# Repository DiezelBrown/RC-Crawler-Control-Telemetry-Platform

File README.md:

# RC Crawler Telemetry Platform
**Project Status:** 🚧 Active Development
<table align="center">
<tr>
<td align="center">
<br>
<b>Custom RC Crawler</b>
</td>

<td align="center">
<br>
<b>Live Telemetry Dashboard</b>
</td>
</tr>
</table>

A custom-built 1/10 scale RC crawler designed to demonstrate embedded systems, wireless telemetry, and real-time vehicle monitoring. The platform combines custom mechanical fabrication with ESP32 firmware, onboard sensors, and Bluetooth Low Energy (BLE) communication.

---

## Features

- ✅ Custom-fabricated steel chassis
- ✅ ESP32 embedded telemetry platform
- ✅ Battery voltage monitoring
- ✅ Motor temperature monitoring
- ✅ Wheel RPM measurement
- ✅ Vehicle speed calculation
- ✅ BNO055 IMU (Pitch & Roll)
- ✅ Bluetooth Low Energy (BLE)
- ✅ Mobile application 
- 🔄  Custom KiCad PCB *(In Progress)*
- ⏳ Operator-assisted recovery mode

---

## Technologies

- C++
- ESP32
- PlatformIO
- Bluetooth Low Energy (BLE)
- Embedded Systems
- Sensor Integration
- I²C
- OneWire
- Hall Effect Sensor
- MIG Welding

---

## Current Telemetry

| Feature | Status |
|----------|--------|
| Battery Voltage | ✅ |
| Motor Temperature | ✅ |
| Wheel RPM | ✅ |
| Vehicle Speed | ✅ |
| Pitch | ✅ |
| Roll | ✅ |
| Bluetooth | ✅ |

---

## Repository Structure

```text
firmware/
├── ESP32 firmware

hardware/
├── BOM.md
├── HARDWARE.md
├── pinout.md
└── wiring.md

docs/
├── Development updates
└── Testing results

photos/
├── Build photos
└── Demonstrations
```

---

## Current Status

### Completed

- ✅ Steel chassis
- ✅ ESP32 firmware
- ✅ Battery voltage sensor
- ✅ DS18B20 temperature sensor
- ✅ Hall-effect RPM sensor
- ✅ BNO055 IMU
- ✅ Bluetooth Low Energy
- ✅  Mobile telemetry application
### In Progress

- 🔄Custom KiCad PCB

### Planned

- ⏳ Operator-assisted recovery mode
- ⏳ Data logging

---

## Future Goals

- Develop a cross-platform mobile application.
- Design a custom KiCad PCB.
- Implement Bluetooth-based operator controls.
- Develop an operator-assisted recovery mode.

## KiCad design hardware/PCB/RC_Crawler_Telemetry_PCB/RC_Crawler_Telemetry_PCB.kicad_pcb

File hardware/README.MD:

# Hardware

## Chassis & Structure
- Custom welded steel chassis
- 5/16 in steel tubing
- 3/16 in steel tubing
- Pothyes CNC aluminum center frame brace / skid plate / transmission mount

## Drivetrain
- INJORA complete SCX10 II gearbox transmission
- 13T pinion gear
- Alloy front steering axle with steel gears (SCX10 II)
- Alloy rear axle with steel gears (SCX10 II)
- MEUS Racing SCX10 II 313 mm link set
- HopsupRC steel driveshaft set (85–122 mm and 95–137 mm)
- HOPLEX heavy-duty driveshaft (125–185 mm)

## Suspension & Steering
- INJORA DRX 100 mm dual-rate oil shocks (4)
- LJWRC 30 kg waterproof digital steering servo

## Wheels & Tires
- 1.9 in aluminum beadlock wheels
- 4.61 in soft rubber crawler tires

## Power System
- HobbyFans S3650 4300KV brushless motor
- HobbyFans 60A waterproof brushless ESC
- ESC programming card
- OVONIC 2S 7.4V 5200 mAh 50C LiPo battery
- Buck converter (5V power for ESP32)

## Radio System
- DumboRC X4 transmitter
- DumboRC X6F receiver

## Telemetry System
- ESP32 DevKit V1
- Battery voltage sensor
- DS18B20 waterproof temperature sensor
- Hall-effect RPM sensor
- BNO055 IMU *(planned)*
- Bluetooth mobile application *(in development)*
- Custom telemetry PCB *(planned)*

## Fasteners & Hardware
- 25 mm mounting screws
- Assorted metric screws
- Lock nuts
- Servo horn
- Steering linkage hardware
- Shock mounting hardware

## Wiring & Electronics
- Breadboard (prototype)
- Jumper wires (prototype)
- Silicone wire *(planned)*
- JST connectors *(planned)*

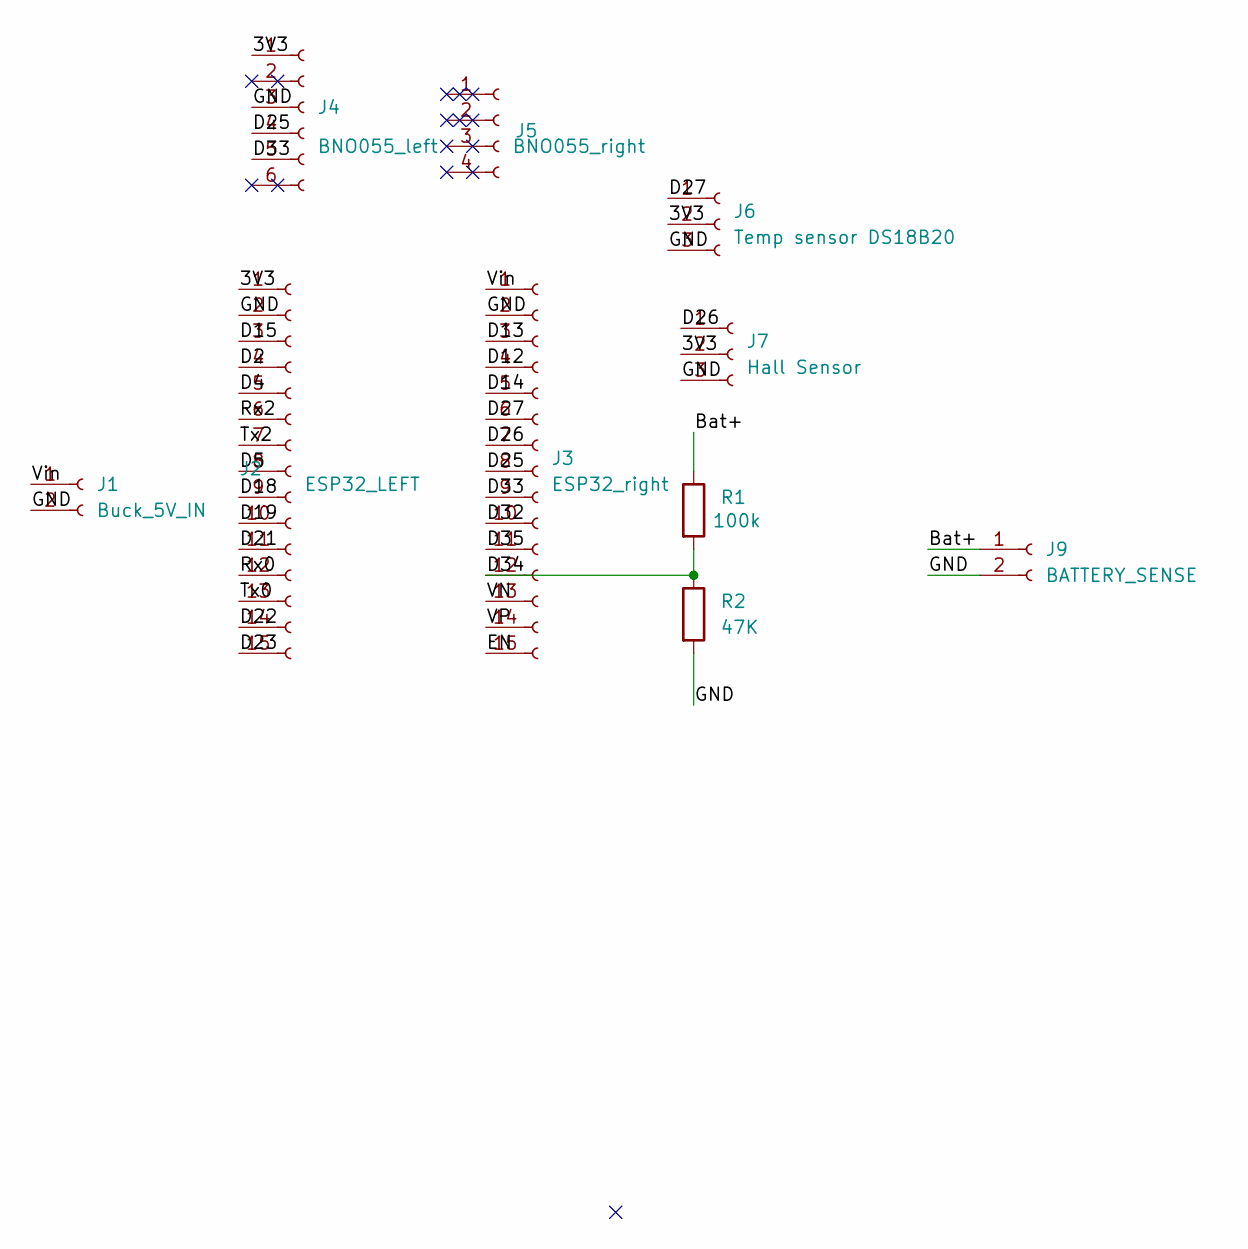
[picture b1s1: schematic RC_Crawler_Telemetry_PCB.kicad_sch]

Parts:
J1: Buck_5V_IN; TerminalBlock_Phoenix_MKDS-1,5-2_1x02_P5.00mm_Horizontal
J2: ESP32_LEFT; PinSocket_1x15_P2.54mm_Vertical
J3: ESP32_right; PinSocket_1x15_P2.54mm_Vertical
J4: BNO055_left; PinSocket_1x06_P2.54mm_Vertical
J5: BNO055_right; PinSocket_1x04_P2.54mm_Vertical
J6: Temp sensor DS18B20; PinSocket_1x03_P2.54mm_Vertical
J7: Hall Sensor; TerminalBlock_Phoenix_MKDS-1,5-3_1x03_P5.00mm_Horizontal
J9: BATTERY_SENSE; TerminalBlock_Phoenix_MKDS-1,5-2_1x02_P5.00mm_Horizontal
R1: 100k; R_Axial_DIN0207_L6.3mm_D2.5mm_P7.62mm_Horizontal
R2: 47K; R_Axial_DIN0207_L6.3mm_D2.5mm_P7.62mm_Horizontal

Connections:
/3V3: J2.1, J4.1, J6.2, J7.2
/Bat+: J9.1, R1.1
/D2: J2.4
/D4: J2.5
/D5: J2.8
/D12: J3.4
/D13: J3.3
/D14: J3.5
/D15: J2.3
/D18: J2.9
/D19: J2.10
/D21: J2.11
/D22: J2.14
/D23: J2.15
/D25: J3.8, J4.4
/D26: J3.7, J7.1
/D27: J3.6, J6.1
/D32: J3.10
/D33: J3.9, J4.5
/D34: J3.12, R1.2, R2.1
/D35: J3.11
/EN: J3.15
/GND: J1.2, J2.2, J3.2, J4.3, J6.3, J7.3, J9.2, R2.2
/Rx0: J2.12
/Rx2: J2.6
/Tx0: J2.13
/Tx2: J2.7
/VN: J3.13
/VP: J3.14
/Vin: J1.1, J3.1

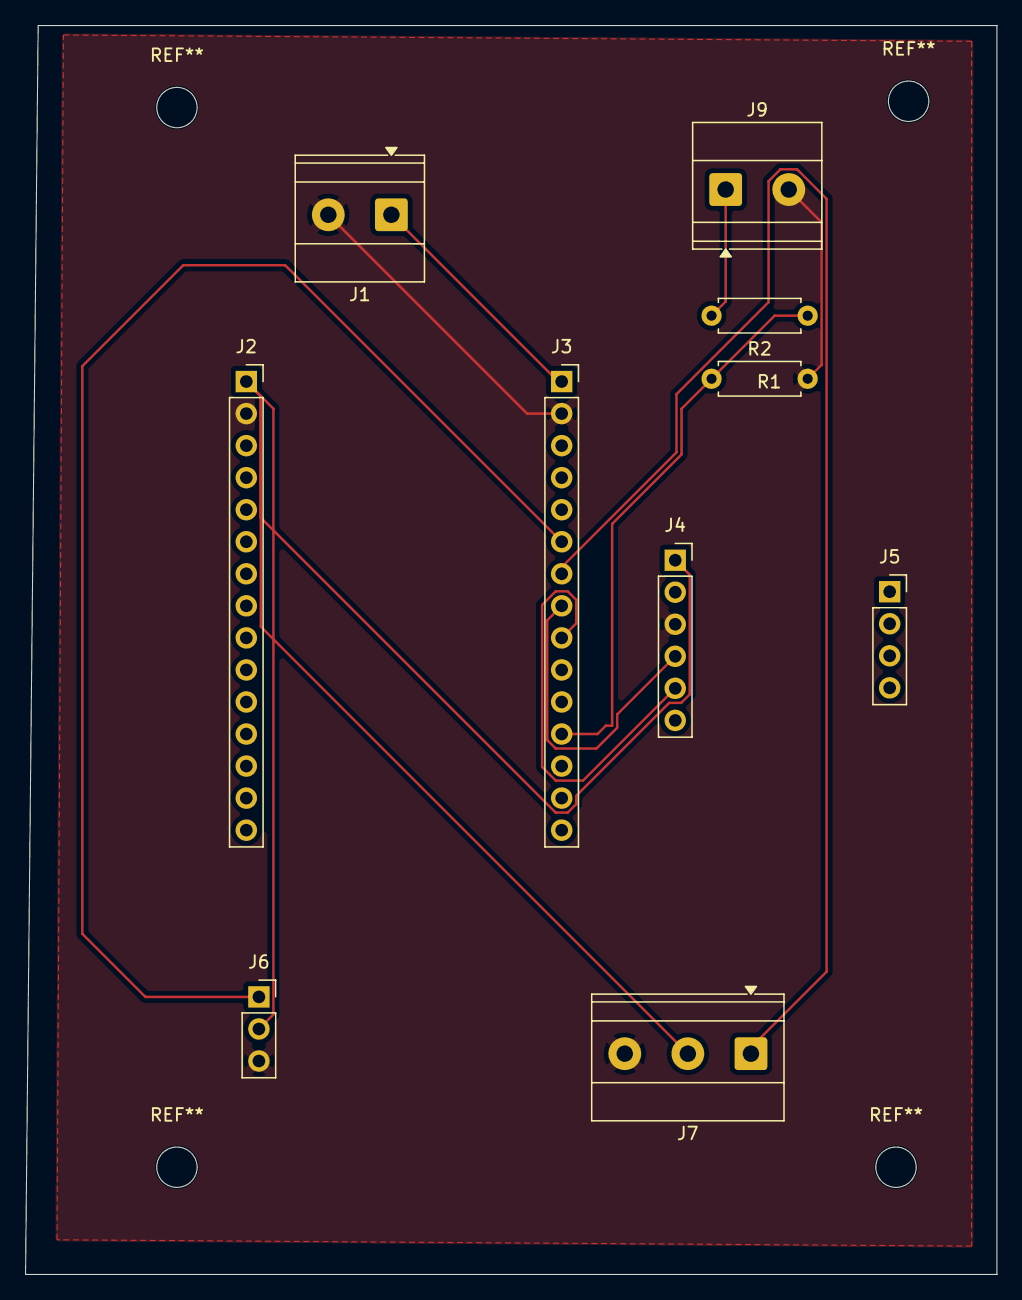
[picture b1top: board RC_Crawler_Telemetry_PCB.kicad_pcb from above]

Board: 2 copper layers, 77.0 x 99.0 mm, 10 parts (0 on the bottom side), 9 nets.

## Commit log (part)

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2026-06-16 Initialize README with project overview
    Add project description for Custom RC Crawler Telemetry System
2026-06-16 Update .gitignore for ESP32 C project
2026-06-16 Add firmware directory
2026-06-16 Add parts list and assembly notes for RC crawler
    Add hardware directory
2026-06-16 Project documentation, wiring diagrams, testing results, and development notes.
2026-06-16 Build progress photos, subsystem integration images, and final project demonstrations.
2026-06-16 Create READ.ME
    Project documentation, wiring diagrams, testing results, and development notes.
2026-06-17 Early Development
2026-06-17 Build progress photos for the Custom RC Crawler Telemetry System.
2026-06-17 Early development
    Chassis development and layout
2026-06-22 Update README with parts list and assembly notes
    Added detailed parts list and assembly notes for the RC crawler, including chassis, drivetrain, suspension, electronics, and planned telemetry system.
2026-06-22 suspension installed
    In the photos I only have the front axle working Im going to install a longer rear driveshaft and then will begin working on my roll cage again
2026-06-22 Rename IMG_3847.jpeg to suspension install
2026-06-22 Rename IMG_3782.jpeg to early development of roll cage
2026-06-22 Rename early development of roll cage to early-development-roll-cage.jpeg
2026-06-22 Add suspension-installed image
2026-06-22 Rename IMG_3783.jpeg to layout.jpg
2026-06-22 Rename IMG_3784.jpeg to Transmission.jpg
2026-06-22 Rename IMG_3786.jpeg to layout2.jpg
2026-06-22 Rename IMG_3847.jpeg to suspension-installed.jpeg
2026-06-22 Rename IMG_3851.jpeg to testing-suspension.jpg
2026-06-22 Update README with RC crawler details and telemetry system
    Added detailed sections for chassis, drivetrain, suspension, wheels, electronics, telemetry system, and hardware.
2026-06-22 Rename 1st build update.pdf to build-update-2026-06-21.md
2026-06-22 Rename build-update-2026-06-21.md to build-update-2026-06-21.pdf
2026-06-22 Rename photos/IMG_3847.jpeg to photos/photos/suspension-installed.jpeg
2026-06-22 Add suspension-installed.jpeg image
2026-06-22 Add suspension-jpeg file
2026-06-22 Rename IMG_3847.jpeg to suspension.jpg
2026-06-22 suspension
2026-06-22 Rename IMG_3847.jpeg to IMG_387.jpeg
2026-06-22 Rename suspension-installed.jpeg to suspension-installed.jpg
2026-06-22 Rename IMG_3847.jpeg to IMG_3847.jpg
2026-06-22 Rename IMG_3847.jpeg to suspension.jpeg
2026-06-22 suspension Installed side View
2026-06-30 test run 6/29
    Today I was able to do the first full test run with my rc car. I the car right now is only running in 2wd and driving in reverse due to the motor having to be mounted differently due to the steep dri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
2026-06-30 Rename IMG_3936 2.mov to testrun.mov
2026-06-30 First test run 6/29
    Today I was able to do the first full test run with my rc car. I the car right now is only running in 2wd and driving in reverse due to the motor having to be mounted differently due to the steep dri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
